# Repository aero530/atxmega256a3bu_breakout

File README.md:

# atxmega256a3bu_breakout

Just a simple breakout board for the atxmega256a3bu.

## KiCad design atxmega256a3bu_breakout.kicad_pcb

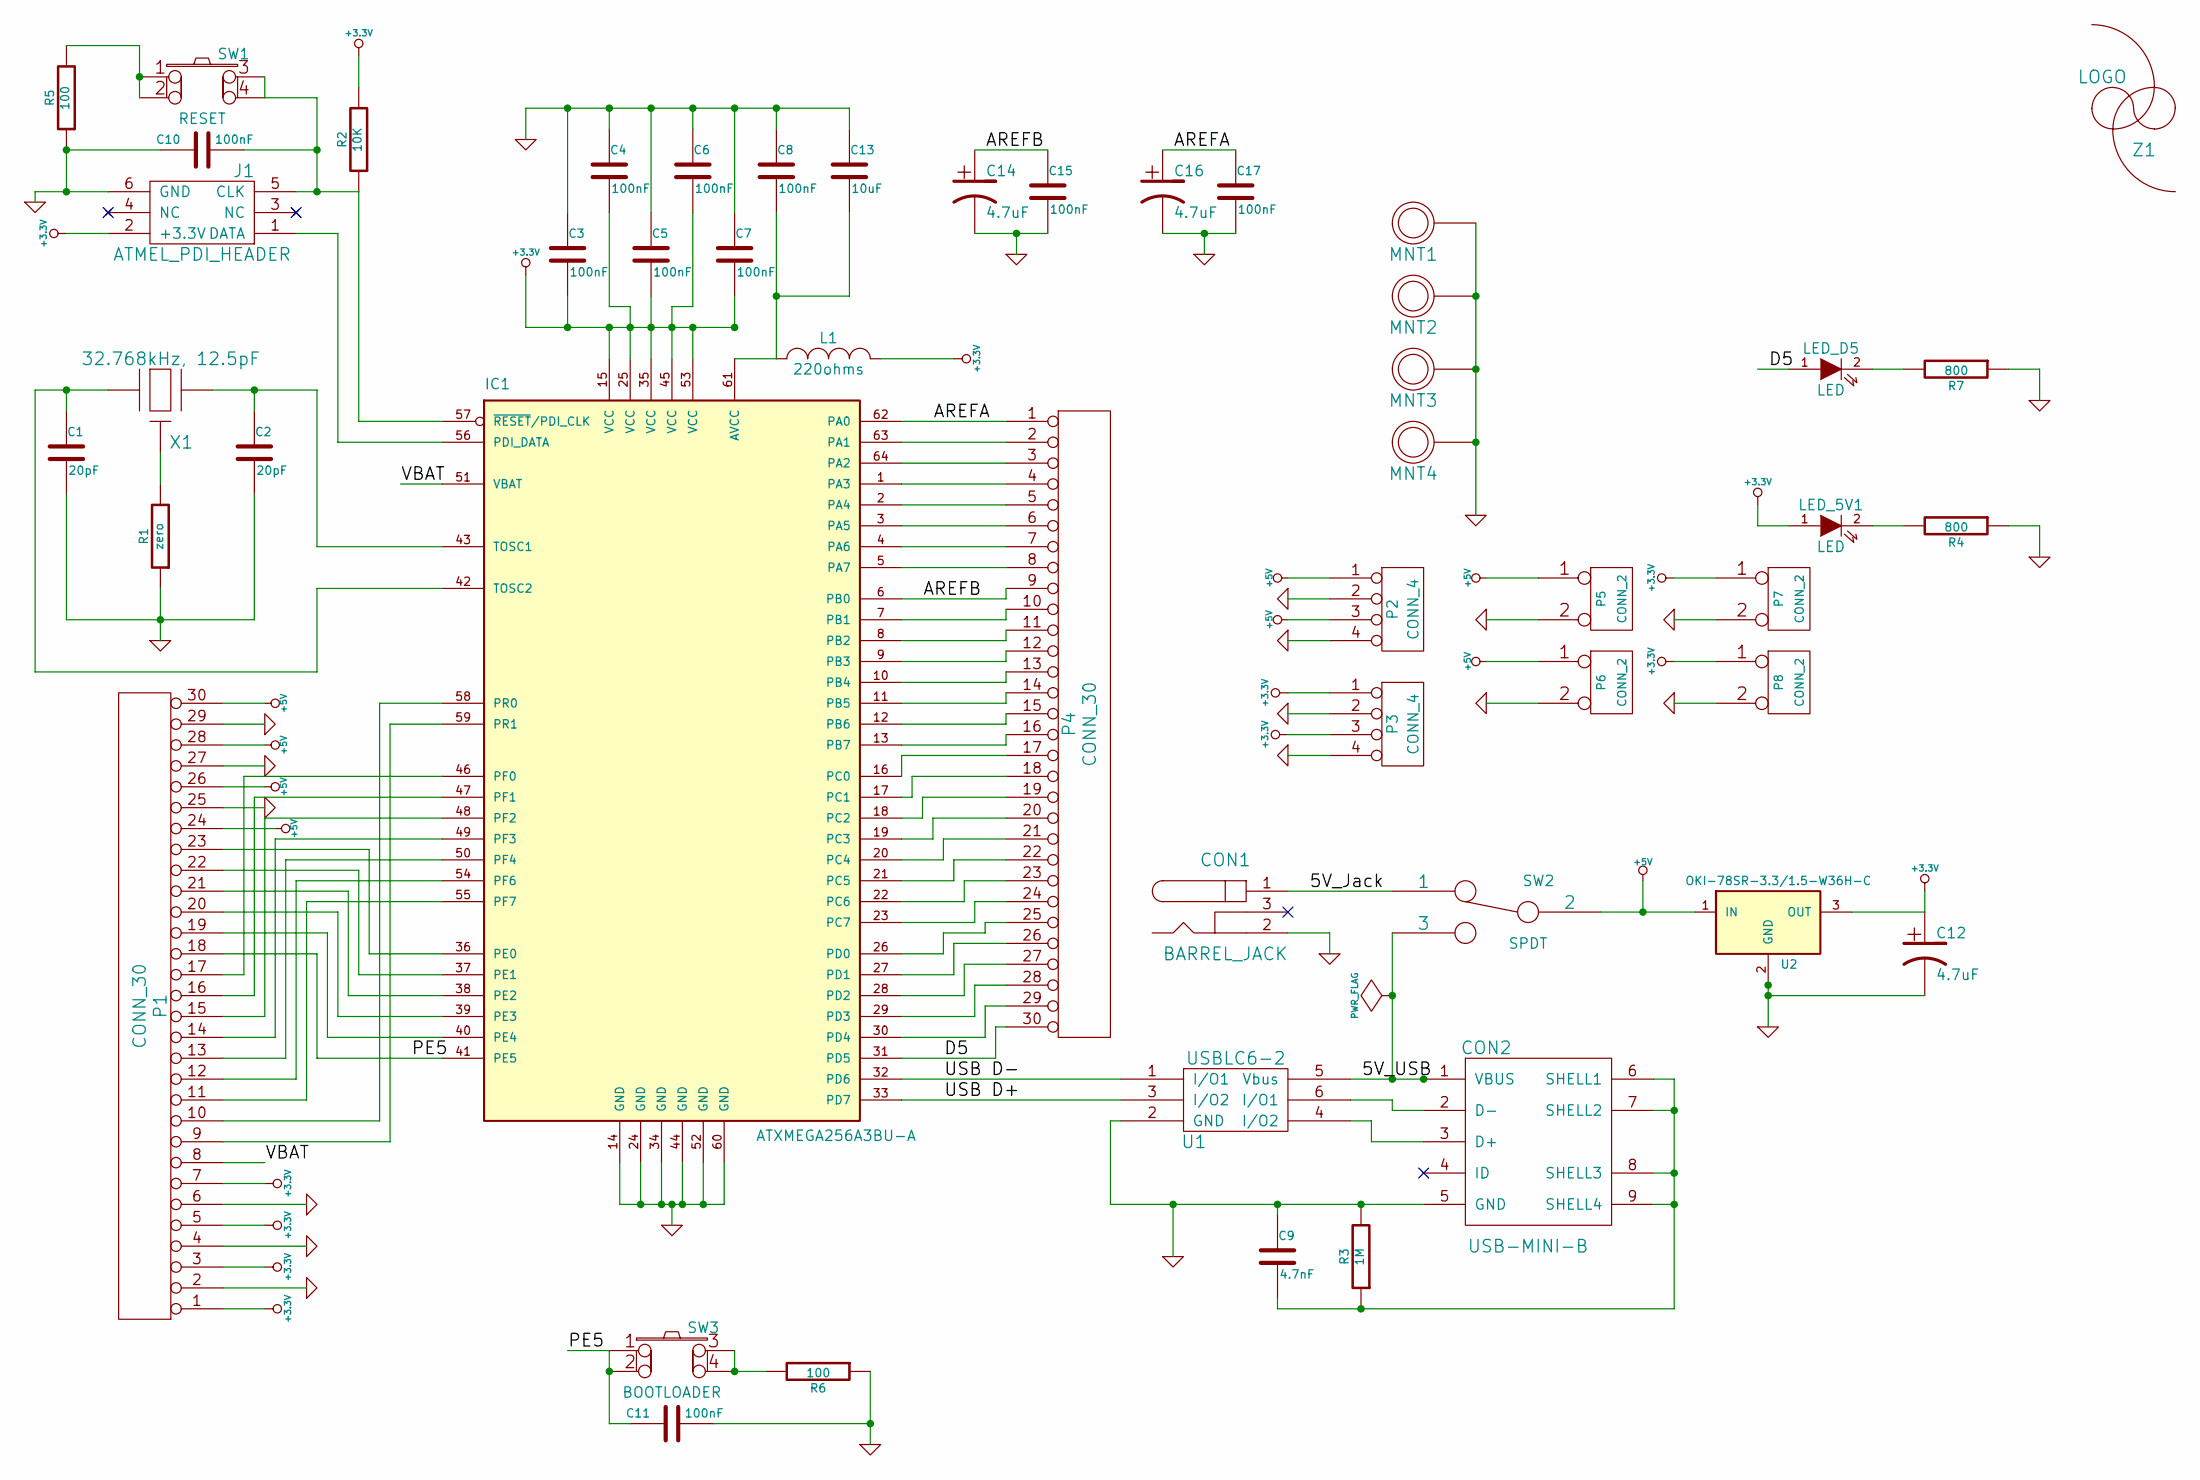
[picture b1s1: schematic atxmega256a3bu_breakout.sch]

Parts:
C1, C2: 20pF
C3, C4, C5, C6, C7, C8, C10, C11, C15, C17: 100nF
C9: 4.7nF
C12, C14, C16: 4.7uF
C13: 10uF
CON1: BARREL_JACK
CON2: USB-MINI-B
IC1: ATXMEGA256A3BU-A; TQFP64
J1: ATMEL_PDI_HEADER
L1: 220ohms; Part Number BLM18AG221SN1D
LED_5V1: LED; Part Number LB Q39G-L2N2-35-1
LED_D5: LED; Part Number LB Q39G-L2N2-35-1
MNT1, MNT2, MNT3, MNT4: 4_40_HOLE
P1, P4: CONN_30
P2, P3: CONN_4
P5, P6, P7, P8: CONN_2
R1: zero
R2: 10K
R3: 1M
R4, R7: 800
R5, R6: 100
SW1: RESET
SW2: SPDT; Part Number 103-12100-EV
SW3: BOOTLOADER
U1: USBLC6-2
U2: OKI-78SR-3.3/1.5-W36H-C; Part Number LM3940IT-3.3/NOPB, OKI-78SR-3.3/1.5-W36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
X1: 32.768kHz, 12.5pF; Part Number AB26TRB-32.768KHZ-T
Z1: LOGO

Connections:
+3.3V: C3.2, C4.2, C5.2, C6.2, C7.2, C12.1, IC1.15 (VCC), IC1.25 (VCC), IC1.35 (VCC), IC1.45 (VCC), IC1.53 (VCC), J1.2 (+3.3V), L1.2, LED_5V1.1 (A), P1.1, P1.3, P1.5, P1.7, P3.1, P3.3, P7.1, P8.1, R2.2, U2.3 (OUT)
+5V: P1.24, P1.26, P1.28, P1.30, P2.1, P2.3, P5.1, P6.1, SW2.2, U2.1 (IN)
/5V_Jack: CON1.1, SW2.1
/5V_USB: CON2.1 (VBUS), SW2.3, U1.5 (Vbus)
/AREFA: C16.1, C17.1, IC1.62 (PA0), P4.1
/AREFB: C14.1, C15.1, IC1.6 (PB0), P4.9
/D5: IC1.31 (PD5), LED_D5.1 (A), P4.30
/PE5: C11.1, IC1.41 (PE5), P1.18, SW3.1, SW3.2
/USB D+: IC1.33 (PD7), U1.3 (I/O2)
/USB D-: IC1.32 (PD6), U1.1 (I/O1)
/VBAT: IC1.51 (VBAT), P1.8
GND: C1.2, C2.2, C3.1, C4.1, C5.1, C6.1, C7.1, C8.1, C9.1, C10.1, C11.2, C12.2, C13.1, C14.2, C15.2, C16.2, C17.2, CON1.2, CON2.5 (GND), IC1.14 (GND), IC1.24 (GND), IC1.34 (GND), IC1.44 (GND), IC1.52 (GND), IC1.60 (GND), J1.6 (GND), MNT1.1, MNT2.1, MNT3.1, MNT4.1, P1.2, P1.4, P1.6, P1.25, P1.27, P1.29, P2.2, P2.4, P3.2, P3.4, P5.2 (PM), P6.2 (PM), P7.2 (PM), P8.2 (PM), R1.1, R3.2, R4.1, R5.1, R6.1, R7.1, U1.2 (GND), U2.2 (GND)
unnamed: IC1.59 (PR1), P1.9
unnamed: IC1.50 (PF4), P1.13
unnamed: IC1.54 (PF6), P1.12
unnamed: IC1.55 (PF7), P1.11
unnamed: IC1.58 (PR0), P1.10
unnamed: IC1.47 (PF1), P1.16
unnamed: IC1.48 (PF2), P1.15
unnamed: IC1.49 (PF3), P1.14
unnamed: IC1.16 (PC0), P4.17
unnamed: IC1.13 (PB7), P4.16
unnamed: IC1.8 (PB2), P4.11
unnamed: IC1.7 (PB1), P4.10
unnamed: IC1.9 (PB3), P4.12
unnamed: IC1.10 (PB4), P4.13
unnamed: IC1.11 (PB5), P4.14
unnamed: IC1.12 (PB6), P4.15
unnamed: C2.1, IC1.43 (TOSC1), X1.1 (X1)
unnamed: IC1.56 (PDI_DATA), J1.1 (DATA)
unnamed: LED_D5.2 (K), R7.2
unnamed: C1.1, IC1.42 (TOSC2), X1.2 (X2)
unnamed: R6.2, SW3.3, SW3.4
unnamed: LED_5V1.2 (K), R4.2
unnamed: CON2.3 (D+), U1.4 (I/O2)
unnamed: CON2.2 (D-), U1.6 (I/O1)
unnamed: C9.2, CON2.6 (SHELL1), CON2.7 (SHELL2), CON2.8 (SHELL3), CON2.9 (SHELL4), R3.1
unnamed: IC1.21 (PC5), P4.22
unnamed: C8.2, C13.2, IC1.61 (AVCC), L1.1
unnamed: IC1.22 (PC6), P4.23
unnamed: IC1.23 (PC7), P4.24
unnamed: IC1.63 (PA1), P4.2
unnamed: IC1.1 (PA3), P4.4
unnamed: IC1.2 (PA4), P4.5
unnamed: IC1.3 (PA5), P4.6
unnamed: IC1.4 (PA6), P4.7
unnamed: IC1.5 (PA7), P4.8
unnamed: IC1.20 (PC4), P4.21
unnamed: IC1.30 (PD4), P4.29
unnamed: IC1.40 (PE4), P1.19
unnamed: IC1.19 (PC3), P4.20
unnamed: IC1.29 (PD3), P4.28
unnamed: IC1.39 (PE3), P1.20
unnamed: R1.2, X1.3 (GND)
unnamed: R5.2, SW1.1, SW1.2
unnamed: C10.2, IC1.57 (~RESET~/PDI_CLK), J1.5 (CLK), R2.1, SW1.3, SW1.4
unnamed: IC1.46 (PF0), P1.17
unnamed: IC1.64 (PA2), P4.3
unnamed: IC1.26 (PD0), P4.25
unnamed: IC1.36 (PE0), P1.23
unnamed: IC1.17 (PC1), P4.18
unnamed: IC1.27 (PD1), P4.26
unnamed: IC1.37 (PE1), P1.22
unnamed: IC1.18 (PC2), P4.19
unnamed: IC1.28 (PD2), P4.27
unnamed: IC1.38 (PE2), P1.21

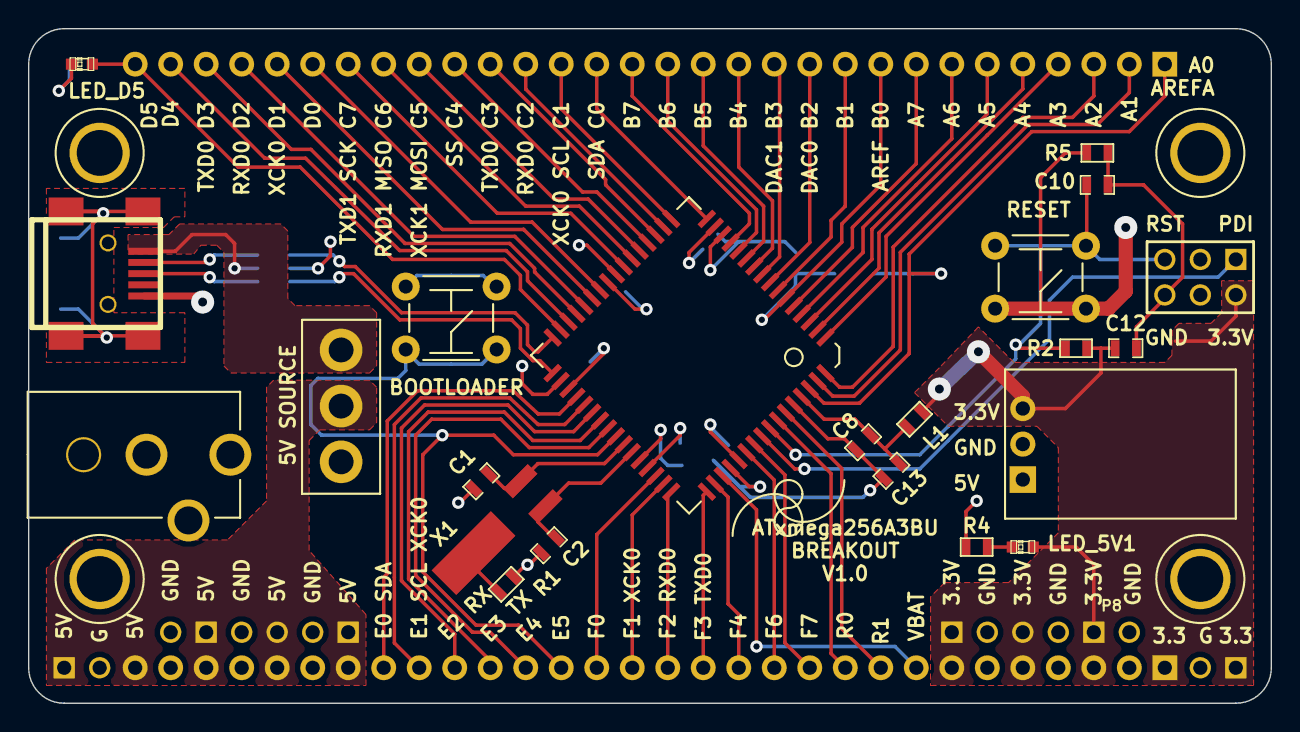
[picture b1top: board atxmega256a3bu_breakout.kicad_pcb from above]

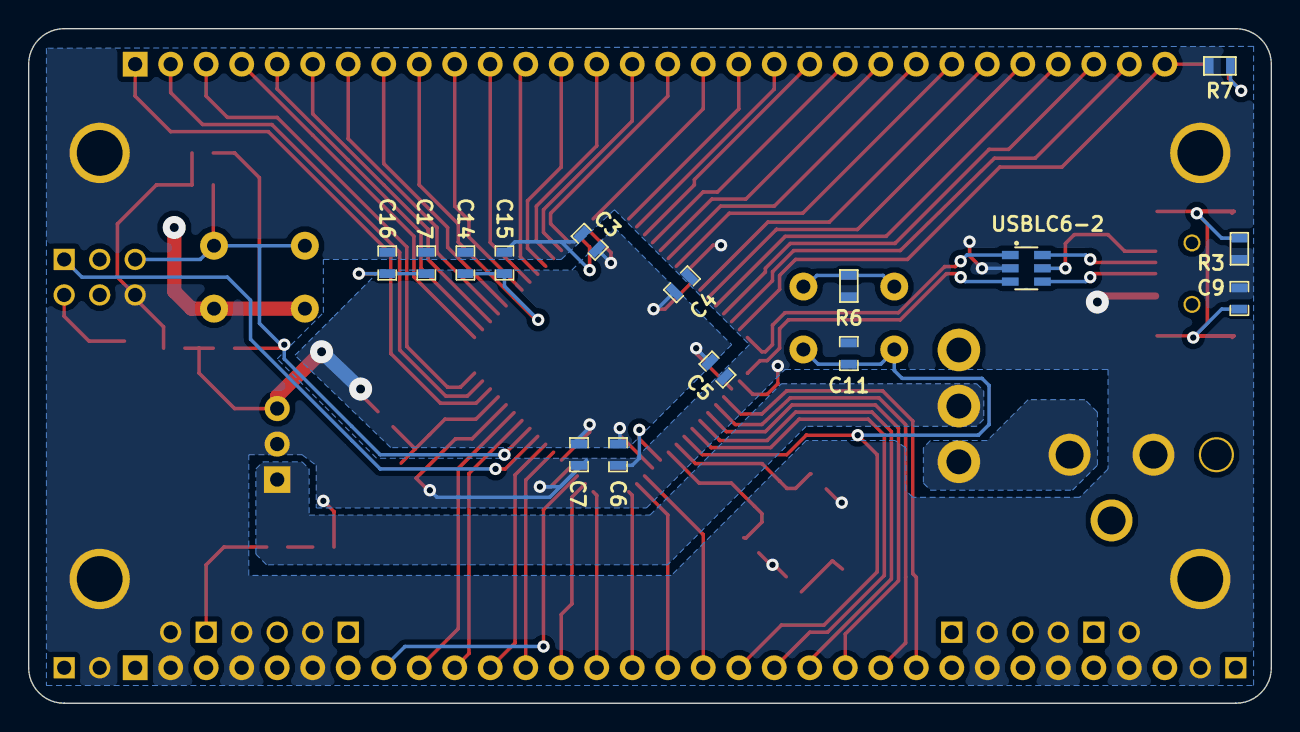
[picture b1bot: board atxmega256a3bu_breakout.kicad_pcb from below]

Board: 2 copper layers, 88.9 x 48.3 mm, 50 parts (15 on the bottom side), 66 nets.

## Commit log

2022-02-24 init
